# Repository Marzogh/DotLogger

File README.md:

# StickLogger (Formerly DotLogger)
A tiny battery powered data logging board based around an ATMega328

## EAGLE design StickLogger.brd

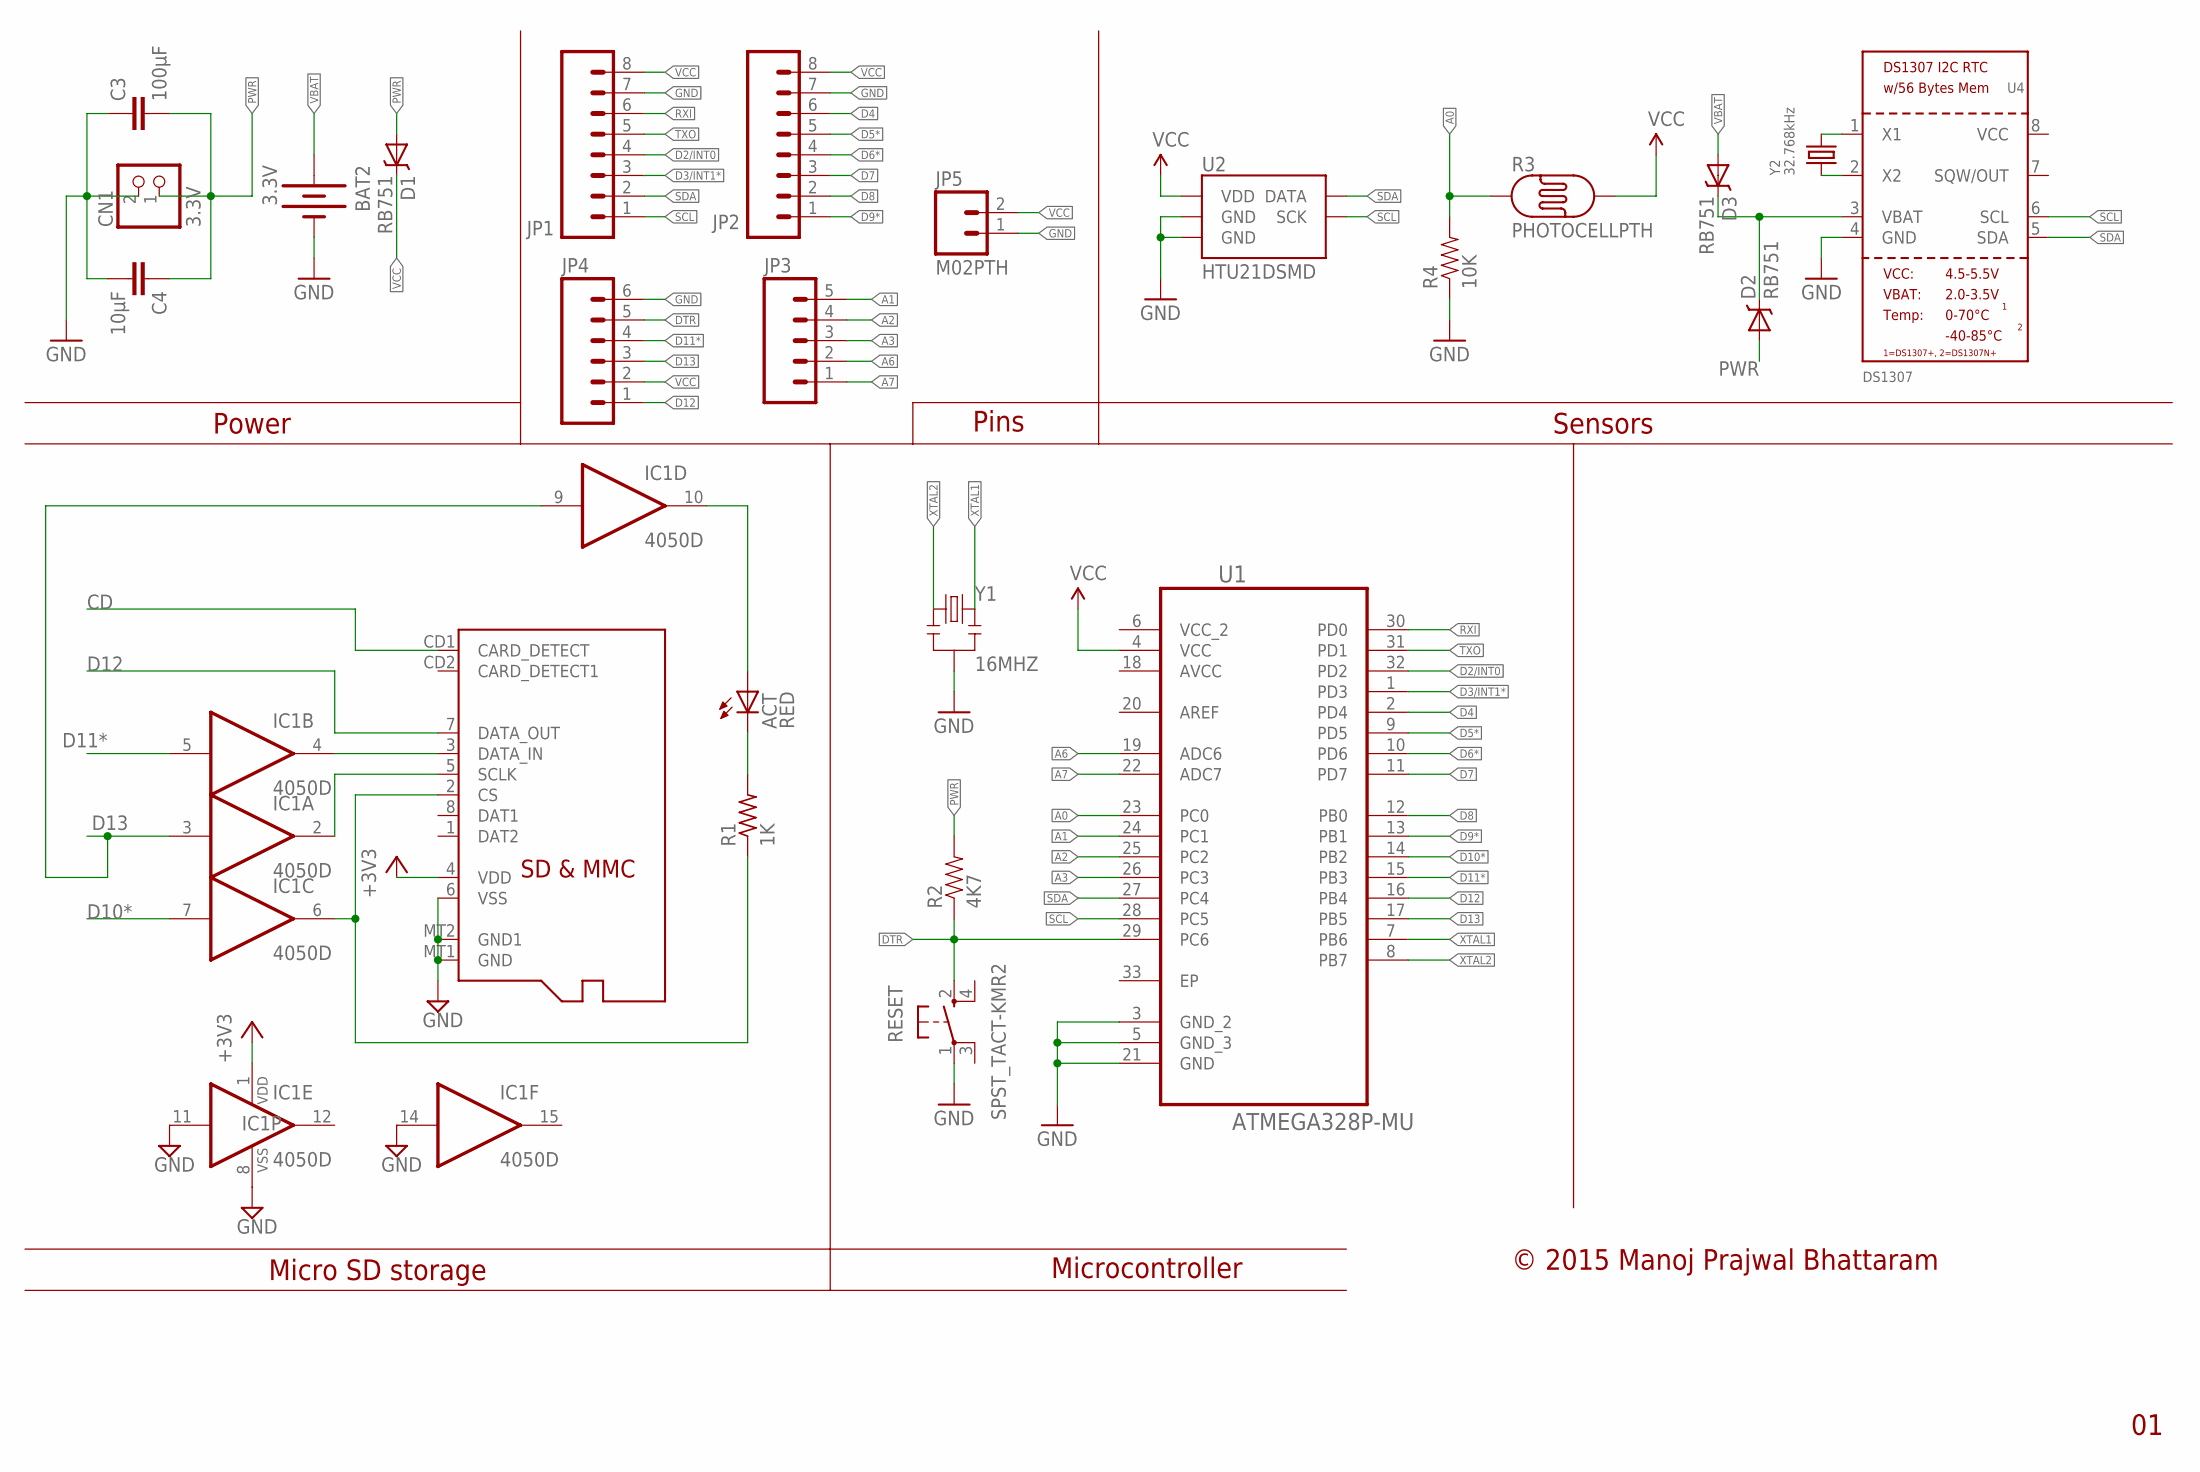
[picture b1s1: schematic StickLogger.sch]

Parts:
ACT: RED; CHIP-LED0805
BAT2: 3.3V; BATTCON_12MM
C3: 100µF; 0402-CAP
C4: 10µF; 0402-CAP
CN1: 3.3V; JST-PH-2-SMT-RA
D1, D2, D3: RB751; SOD-523
IC1: 4050D; SO16
JP1, JP2: M08NO_SILK; 1X08_NO_SILK
JP3: M05NO_SILK; 1X05_NO_SILK
JP4: M06SMD; 1X06-SMD
JP5: M02PTH; 1X02
R1: 1K; R0805
R2: 4K7; 0402-RES
R3: PHOTOCELLPTH; PHOTOCELL
R4: 10K; 0402-RES
RESET: SPST_TACT-KMR2; KMR2
U1: ATMEGA328P-MU; QFN50P500X500X100-33N
U2: HTU21DSMD; HTU21D
U4: DS1307; SOIC8_150MIL
X1: MICROSD
Y1: 16MHZ; RESONATOR-SMD
Y2: 32.768kHz; CRYSTAL-32KHZ-SMD

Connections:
3V: D2.C, D3.C, U4.3 (VBAT)
+3V3: IC1.1 (VDD), X1.4 (VDD)
A0: R3.1, R4.2, U1.23 (PC0)
A1: JP3.5, U1.24 (PC1)
A2: JP3.4, U1.25 (PC2)
A3: JP3.3, U1.26 (PC3)
A6: JP3.2, U1.19 (ADC6)
A7: JP3.1, U1.22 (ADC7)
AVCC: U1.18 (AVCC)
CD: X1.CD1 (CARD_DETECT)
D2/INT0: JP1.4, U1.32 (PD2)
D3/INT1*: JP1.3, U1.1 (PD3)
D4: JP2.6, U1.2 (PD4)
D5*: JP2.5, U1.9 (PD5)
D6*: JP2.4, U1.10 (PD6)
D7: JP2.3, U1.11 (PD7)
D8: JP2.2, U1.12 (PB0)
D9*: JP2.1, U1.13 (PB1)
D10*: IC1.7 (I), U1.14 (PB2)
D11*: IC1.5 (I), JP4.4, U1.15 (PB3)
D12: JP4.1, U1.16 (PB4), X1.7 (DATA_OUT)
D13: IC1.3 (I), IC1.9 (I), JP4.3, U1.17 (PB5)
DTR: JP4.5, R2.1, RESET.2 (S), U1.29 (PC6)
GND: BAT2.GND (-), C3.1, C4.2, CN1.2 (1), IC1.8 (VSS), IC1.11 (I), IC1.14 (I), JP1.7, JP2.7, JP4.6, JP5.1, R4.1, RESET.1, U1.3 (GND_2), U1.5 (GND_3), U1.21 (GND), U2.7 (GND), U2.GND, U4.4 (GND), X1.6 (VSS), X1.MT1 (GND), X1.MT2 (GND1), Y1.2
unnamed: ACT.A, IC1.10 (O)
unnamed: IC1.2 (O), X1.5 (SCLK)
unnamed: IC1.6 (O), R1.1, X1.2 (CS)
unnamed: ACT.C, R1.2
unnamed: IC1.4 (O), X1.3 (DATA_IN)
unnamed: U4.2 (X2), Y2.X1 (1)
unnamed: U4.1 (X1), Y2.X2 (2)
PWR: C3.2, C4.1, CN1.1 (2), D1.A, D2.A, R2.2
RXI: JP1.6, U1.30 (PD0)
SCL: JP1.1, U1.28 (PC5), U2.SCK, U4.6 (SCL)
SDA: JP1.2, U1.27 (PC4), U2.DATA, U4.5 (SDA)
TXO: JP1.5, U1.31 (PD1)
VBAT: BAT2.PWR@1 (+), D3.A
VCC: D1.C, JP1.8, JP2.8, JP4.2, JP5.2, R3.2, U1.4 (VCC), U2.VDD
VCC_2: U1.6 (VCC_2)
XTAL1: U1.7 (PB6), Y1.3
XTAL2: U1.8 (PB7), Y1.1

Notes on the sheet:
© 2015 Manoj Prajwal Bhattaram
Power
Micro SD storage
Pins
Microcontroller
Sensors

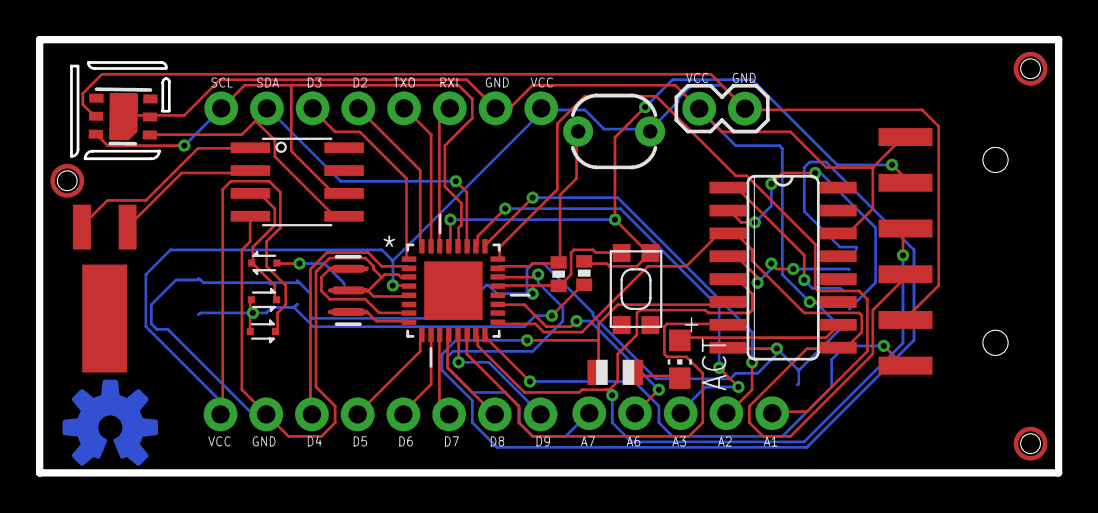
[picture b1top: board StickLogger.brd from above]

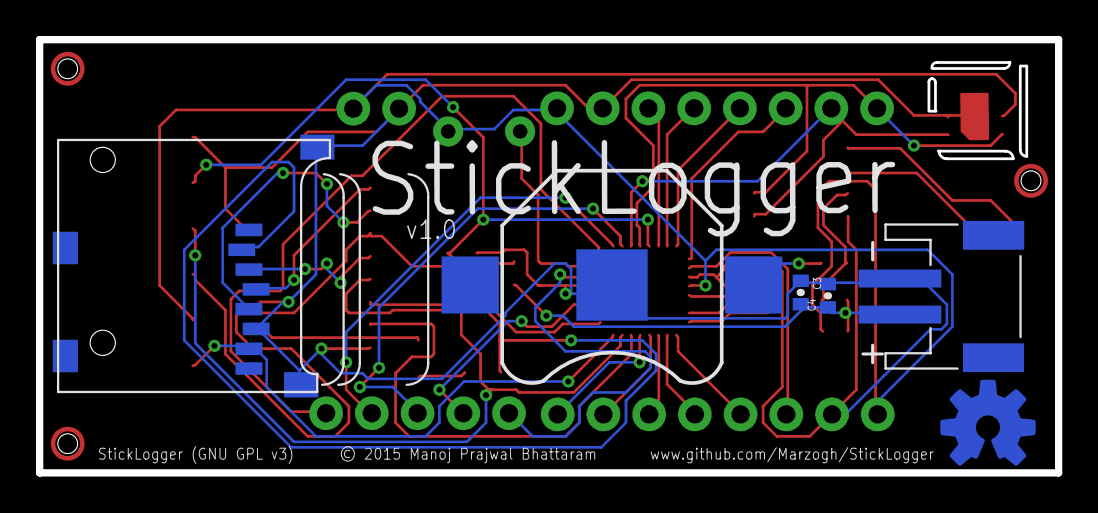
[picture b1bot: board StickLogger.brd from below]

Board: 2 copper layers, 56.6 x 24.1 mm, 26 parts (6 on the bottom side), 38 nets.

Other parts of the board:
U$1: OSHWLOGO_TOP_0.2

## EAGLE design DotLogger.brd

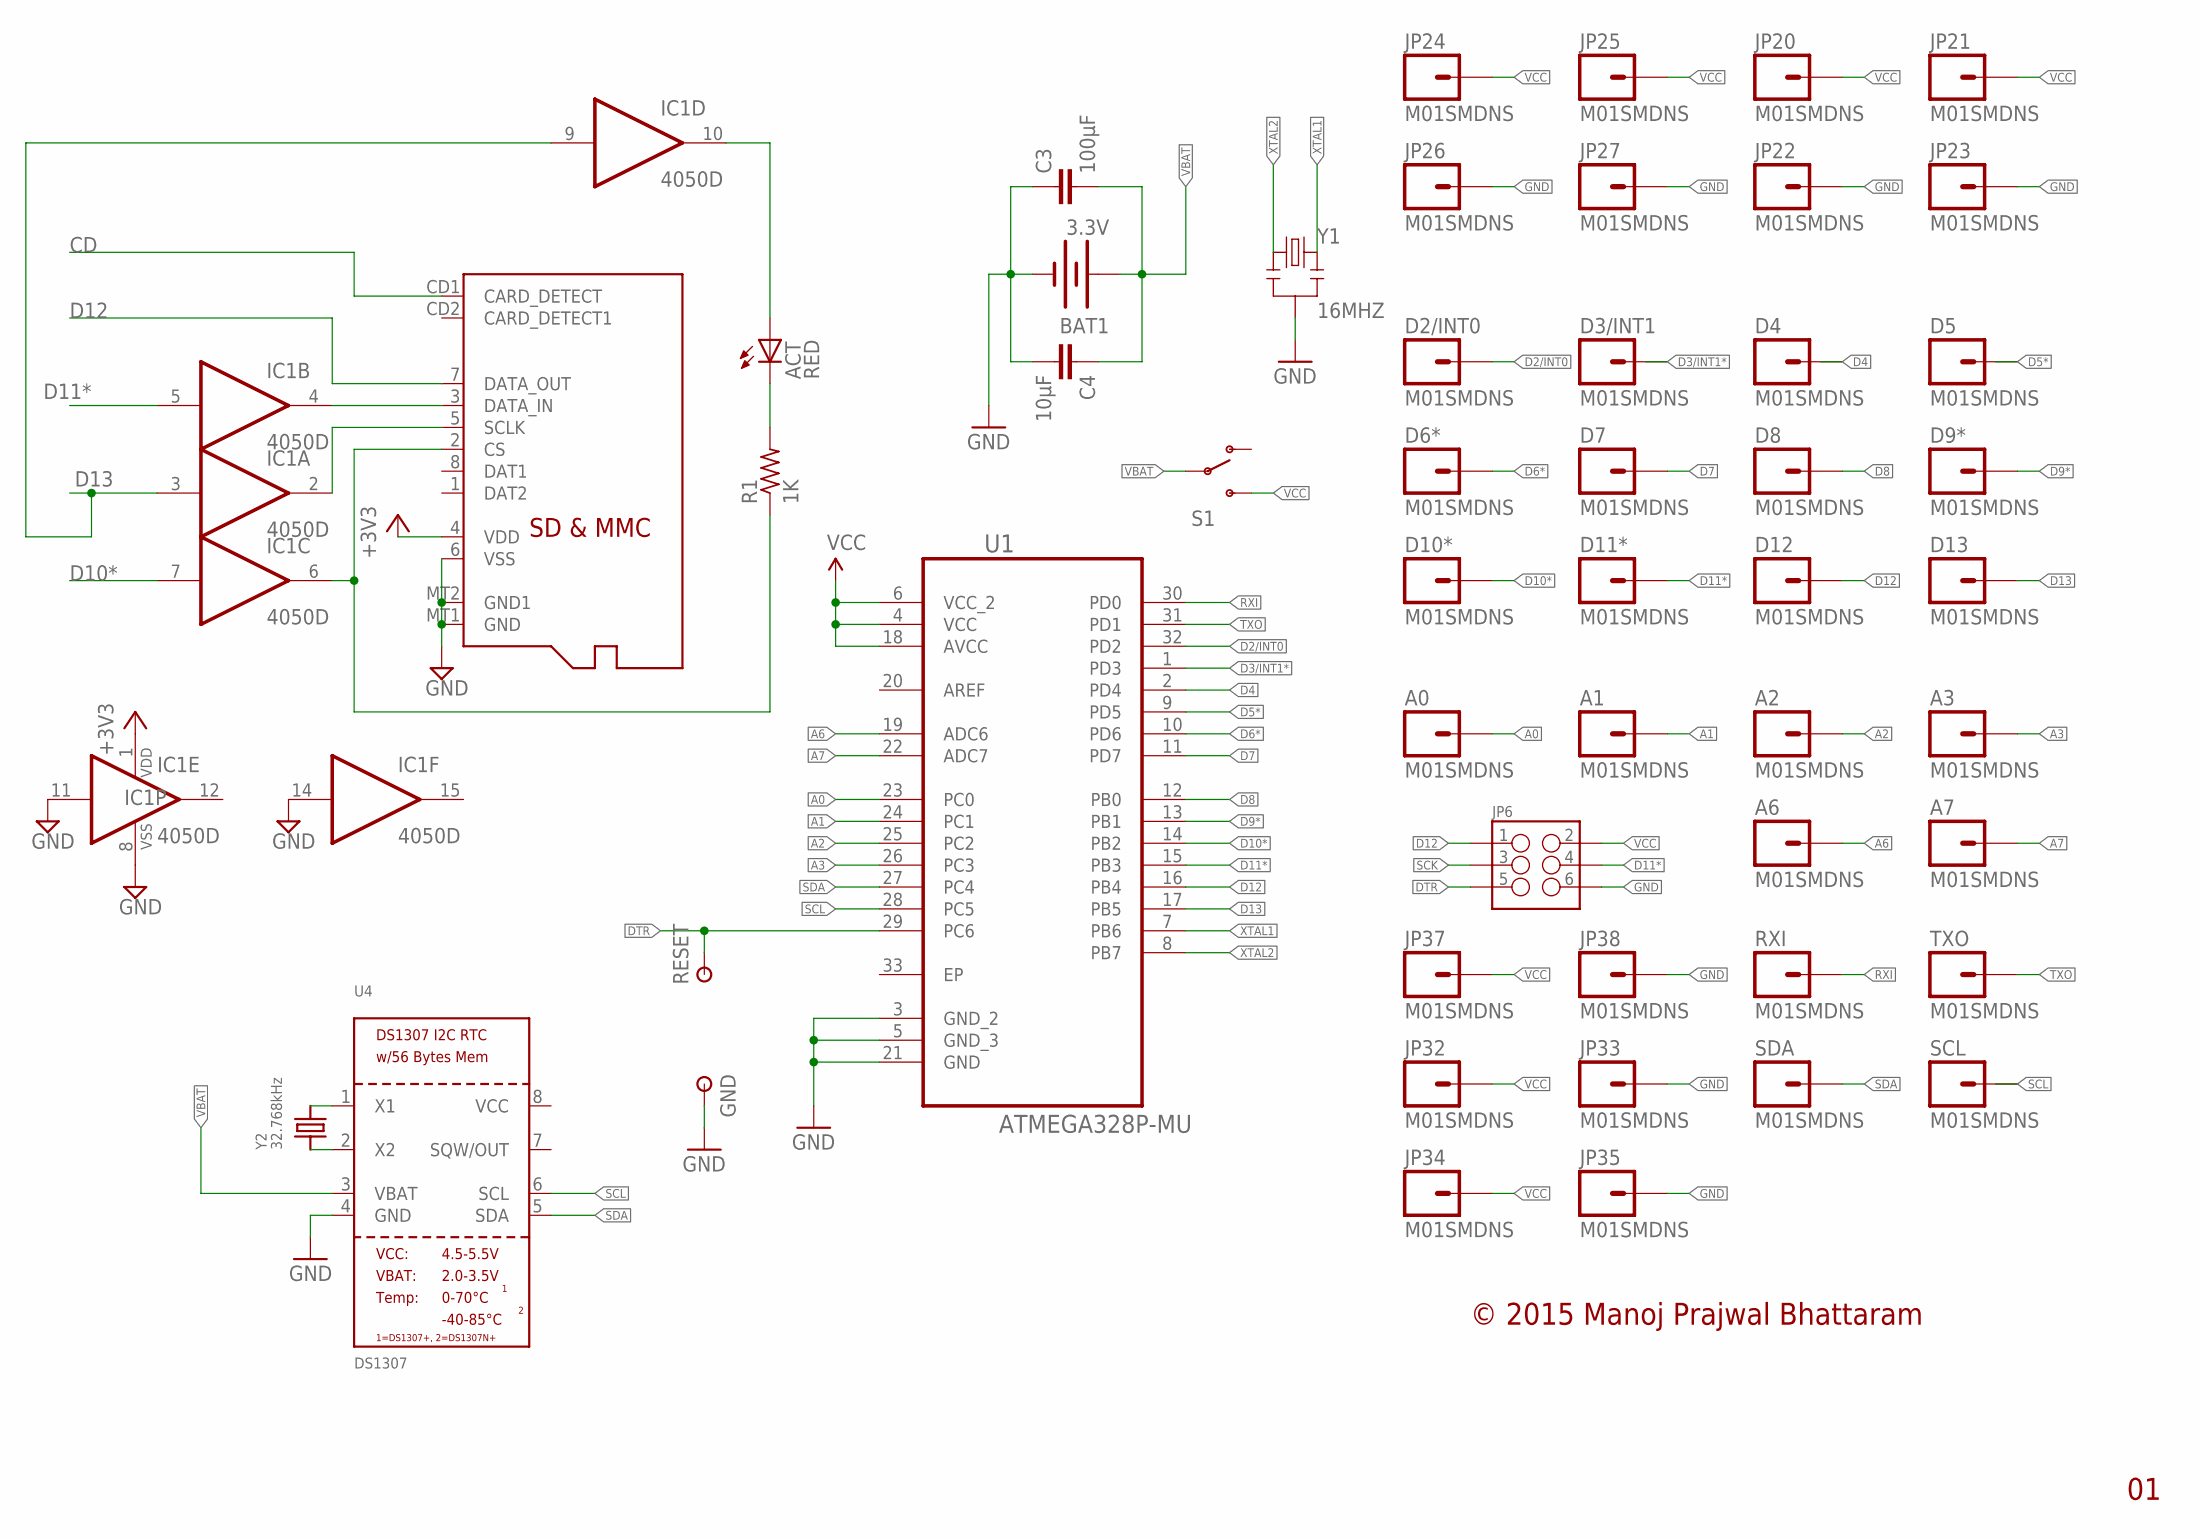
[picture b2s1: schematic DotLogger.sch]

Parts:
A0, A1, A2, A3, A6, A7: M01SMDNS; 1X01NS
ACT: RED; CHIP-LED0805
BAT1: 3.3V; BATTCON_20MM
C3: 100µF; 0402-CAP
C4: 10µF; 0402-CAP
D2/INT0, D3/INT1, D4, D5, D6*, D7, D8, D9*, D10*, D11*, D12, D13: M01SMDNS; 1X01NS
GND: PAD-TESTPOINT; 1,6/0,8
IC1: 4050D; SO16
JP6: M03X2POGO_PINS; 2X3_POGO
JP20, JP21, JP22, JP23, JP24, JP25, JP26, JP27, JP32, JP33, JP34, JP35, JP37, JP38: M01SMDNS; 1X01NS
R1: 1K; R0805
RESET: PAD-TESTPOINT; 1,6/0,8
RXI: M01SMDNS; 1X01NS
S1: SWITCH-SPDT-SMD-A; SWITCH-SPST-SMD-A
SCL: M01SMDNS; 1X01NS
SDA: M01SMDNS; 1X01NS
TXO: M01SMDNS; 1X01NS
U1: ATMEGA328P-MU; QFN50P500X500X100-33N
U4: DS1307; SOIC8_150MIL
X1: MICROSD
Y1: 16MHZ; RESONATOR-SMD
Y2: 32.768kHz; CRYSTAL_8X3.8

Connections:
+3V3: IC1.1 (VDD), X1.4 (VDD)
A0: A0.1, U1.23 (PC0)
A1: A1.1, U1.24 (PC1)
A2: A2.1, U1.25 (PC2)
A3: A3.1, U1.26 (PC3)
A6: A6.1, U1.19 (ADC6)
A7: A7.1, U1.22 (ADC7)
CD: X1.CD1 (CARD_DETECT)
D2/INT0: D2/INT0.1, U1.32 (PD2)
D3/INT1*: D3/INT1.1, U1.1 (PD3)
D4: D4.1, U1.2 (PD4)
D5*: D5.1, U1.9 (PD5)
D6*: D6*.1, U1.10 (PD6)
D7: D7.1, U1.11 (PD7)
D8: D8.1, U1.12 (PB0)
D9*: D9*.1, U1.13 (PB1)
D10*: D10*.1, IC1.7 (I), U1.14 (PB2)
D11*: D11*.1, IC1.5 (I), JP6.P$4 (4), U1.15 (PB3)
D12: D12.1, JP6.P$1 (1), U1.16 (PB4), X1.7 (DATA_OUT)
D13: D13.1, IC1.3 (I), IC1.9 (I), U1.17 (PB5)
DTR: JP6.P$5 (5), RESET.1, U1.29 (PC6)
GND: BAT1.2 (-), C3.1, C4.2, GND.1, IC1.8 (VSS), IC1.11 (I), IC1.14 (I), JP6.P$6 (6), JP22.1, JP23.1, JP26.1, JP27.1, JP33.1, JP35.1, JP38.1, U1.3 (GND_2), U1.5 (GND_3), U1.21 (GND), U4.4 (GND), X1.6 (VSS), X1.MT1 (GND), X1.MT2 (GND1), Y1.2
unnamed: ACT.A, IC1.10 (O)
unnamed: IC1.2 (O), X1.5 (SCLK)
unnamed: IC1.6 (O), R1.1, X1.2 (CS)
unnamed: ACT.C, R1.2
unnamed: IC1.4 (O), X1.3 (DATA_IN)
unnamed: U4.2 (X2), Y2.P$1 (1)
unnamed: U4.1 (X1), Y2.P$4 (2)
RXI: RXI.1, U1.30 (PD0)
SCK: JP6.P$3 (3)
SCL: SCL.1, U1.28 (PC5), U4.6 (SCL)
SDA: SDA.1, U1.27 (PC4), U4.5 (SDA)
TXO: TXO.1, U1.31 (PD1)
VBAT: BAT1.1 (+), C3.2, C4.1, S1.2, U4.3 (VBAT)
VCC: JP6.P$2 (2), JP20.1, JP21.1, JP24.1, JP25.1, JP32.1, JP34.1, JP37.1, S1.3 (S), U1.4 (VCC), U1.6 (VCC_2), U1.18 (AVCC)
XTAL1: U1.7 (PB6), Y1.3
XTAL2: U1.8 (PB7), Y1.1

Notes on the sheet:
© 2015 Manoj Prajwal Bhattaram

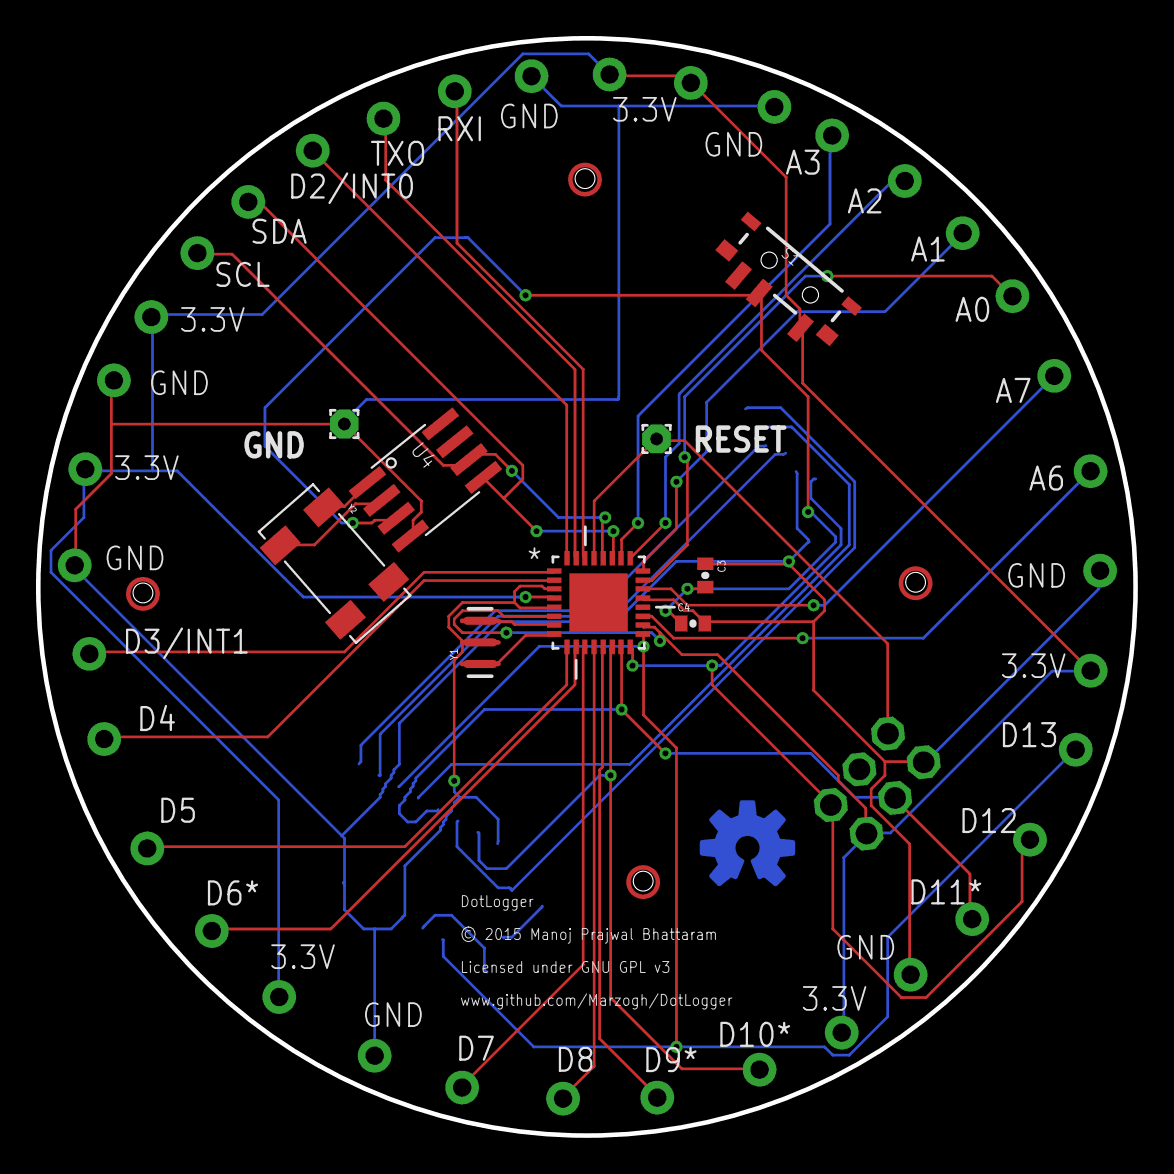
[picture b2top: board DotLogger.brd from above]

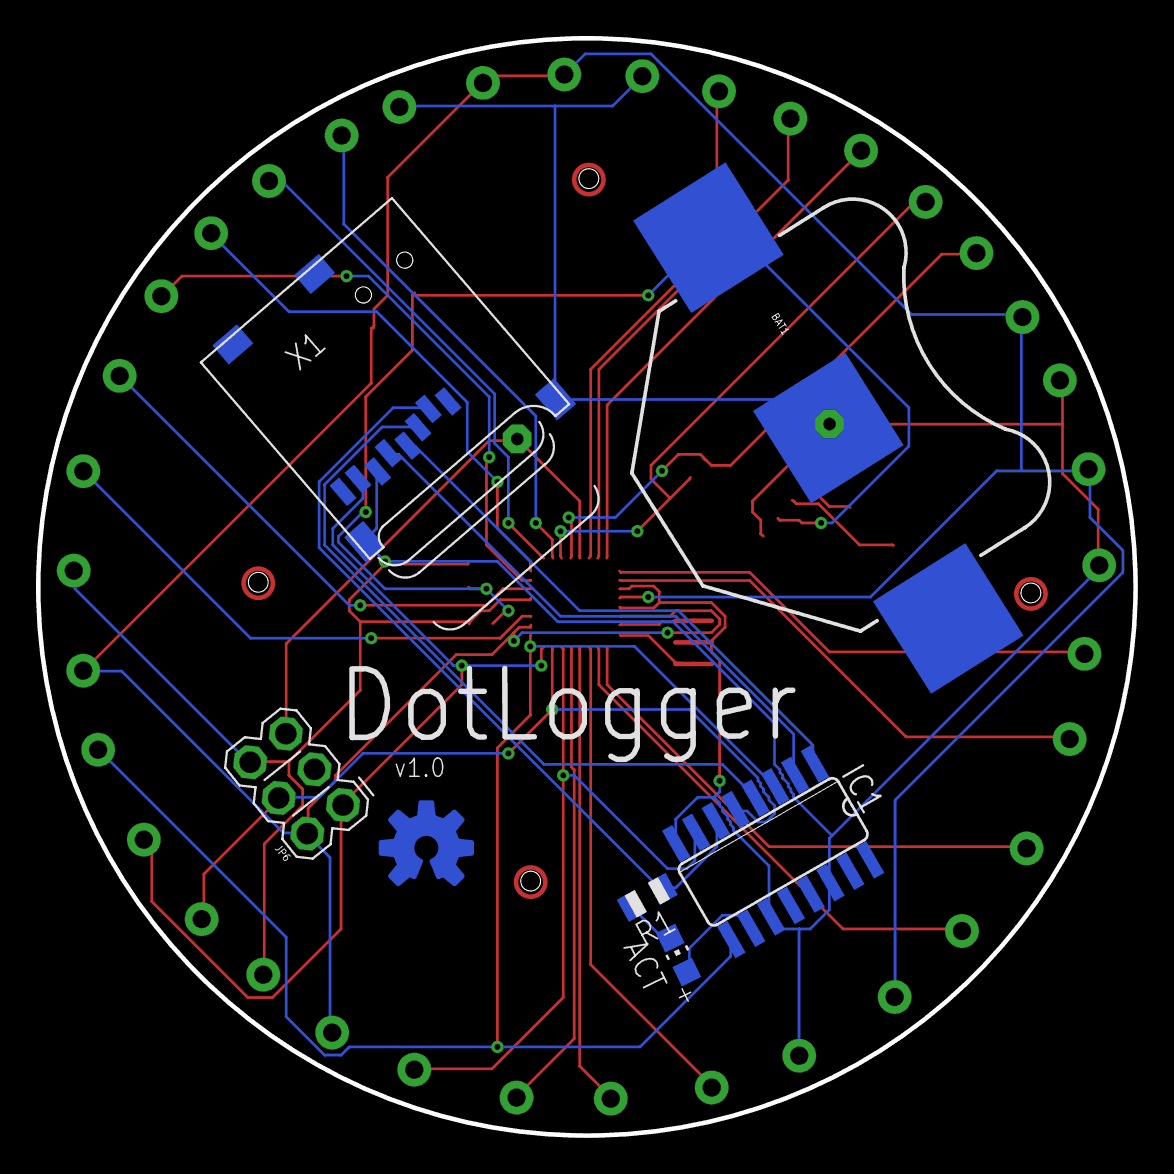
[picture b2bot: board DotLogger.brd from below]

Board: 2 copper layers, 61.0 x 61.0 mm, 52 parts (7 on the bottom side), 36 nets.

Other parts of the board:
U$1: OSHWLOGO_TOP_0.2

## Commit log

2015-05-09 Schematics, Board design and Gerber files added
2015-08-08 Renamed project to StickLogger
    New board design

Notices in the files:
DotLogger.brd:
Licensed under GNU GPL v3
StickLogger.brd:
StickLogger (GNU GPL v3) © 2015 Manoj Prajwal Bhattaram www.github.com/Marzogh/StickLogger
parts and their libraries:
SparkFun-Capacitors: Licensing: Creative Commons ShareAlike 4.0 International - https://creativecommons.org/licenses/by-sa/4.0
